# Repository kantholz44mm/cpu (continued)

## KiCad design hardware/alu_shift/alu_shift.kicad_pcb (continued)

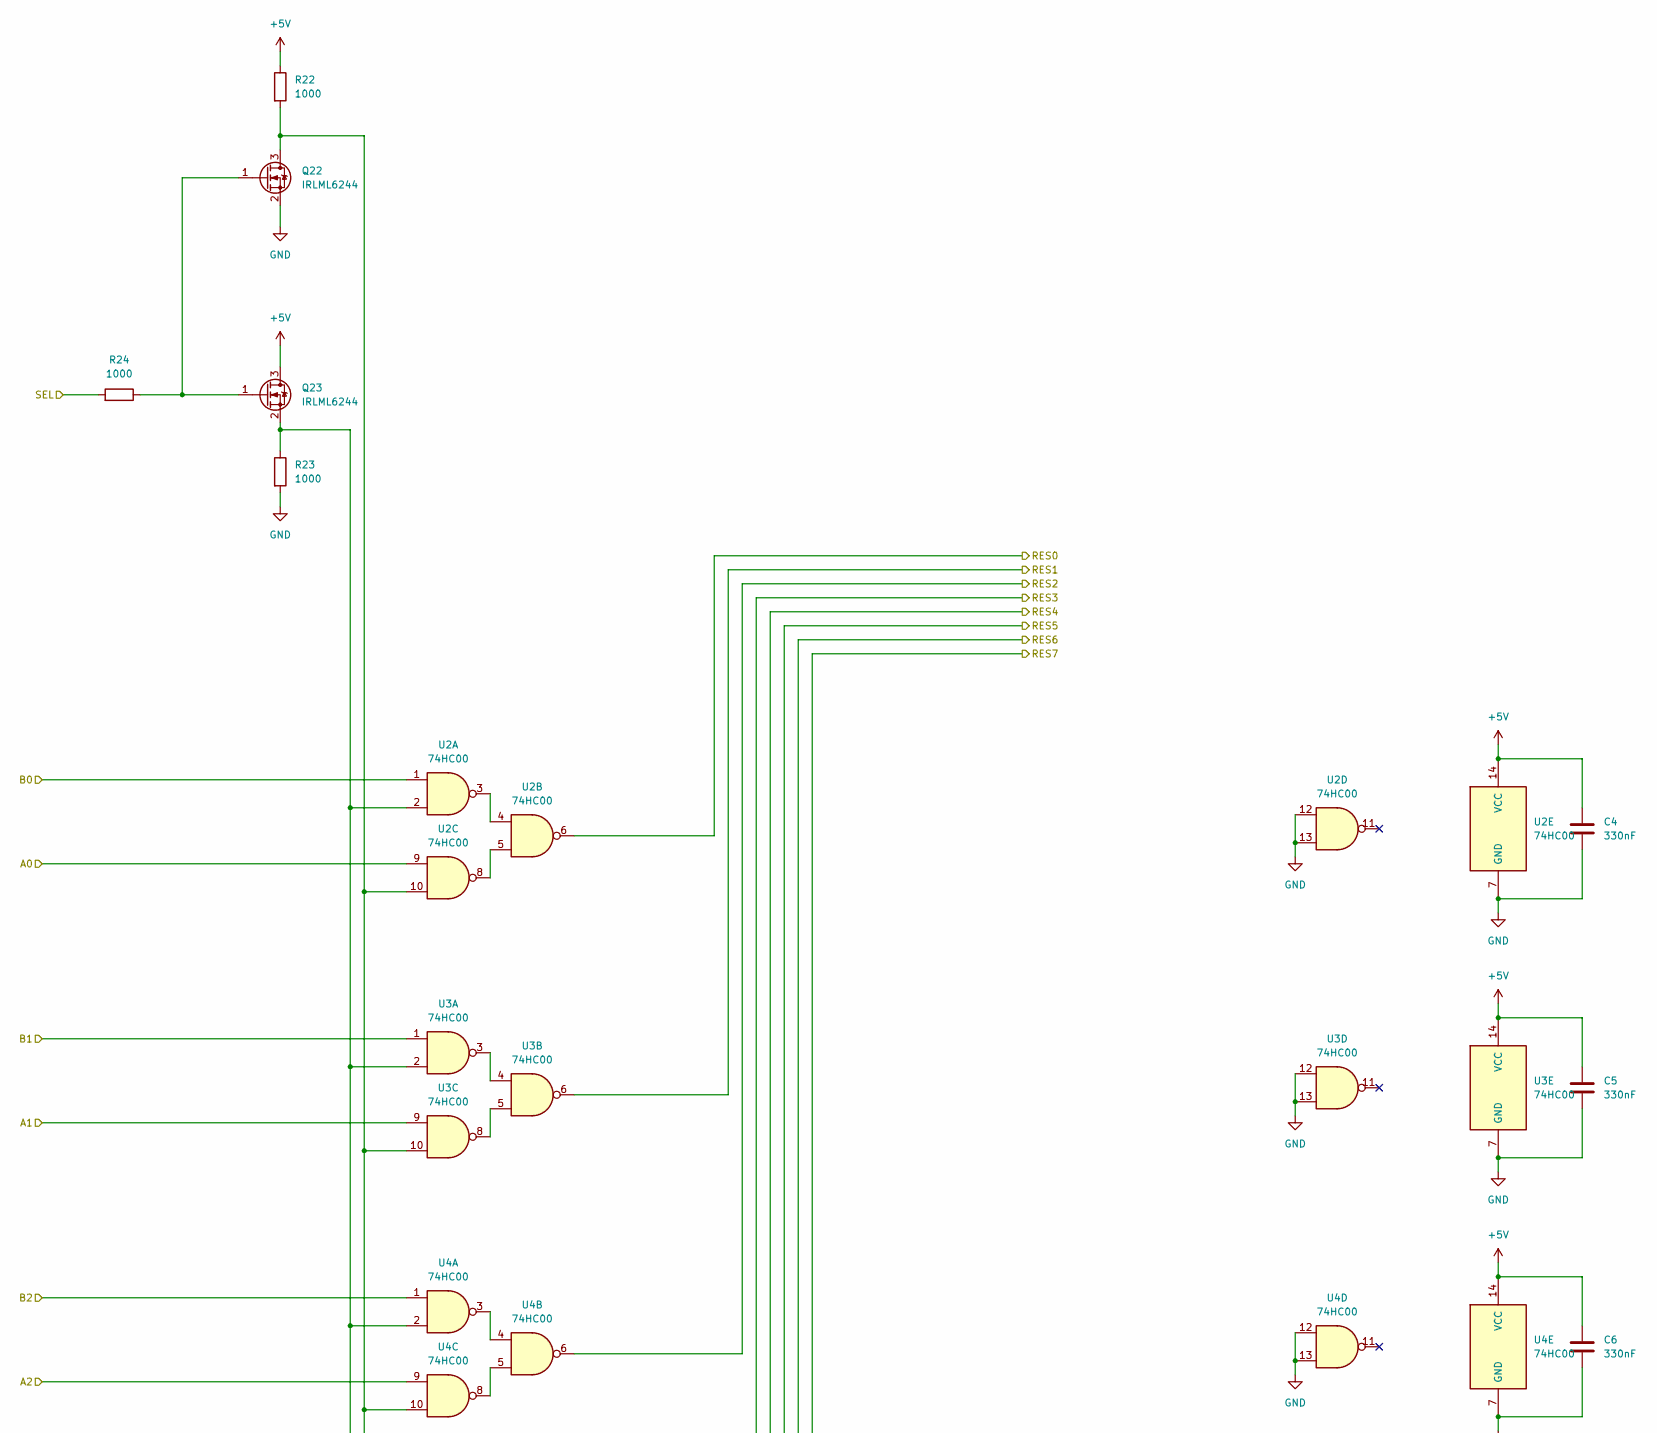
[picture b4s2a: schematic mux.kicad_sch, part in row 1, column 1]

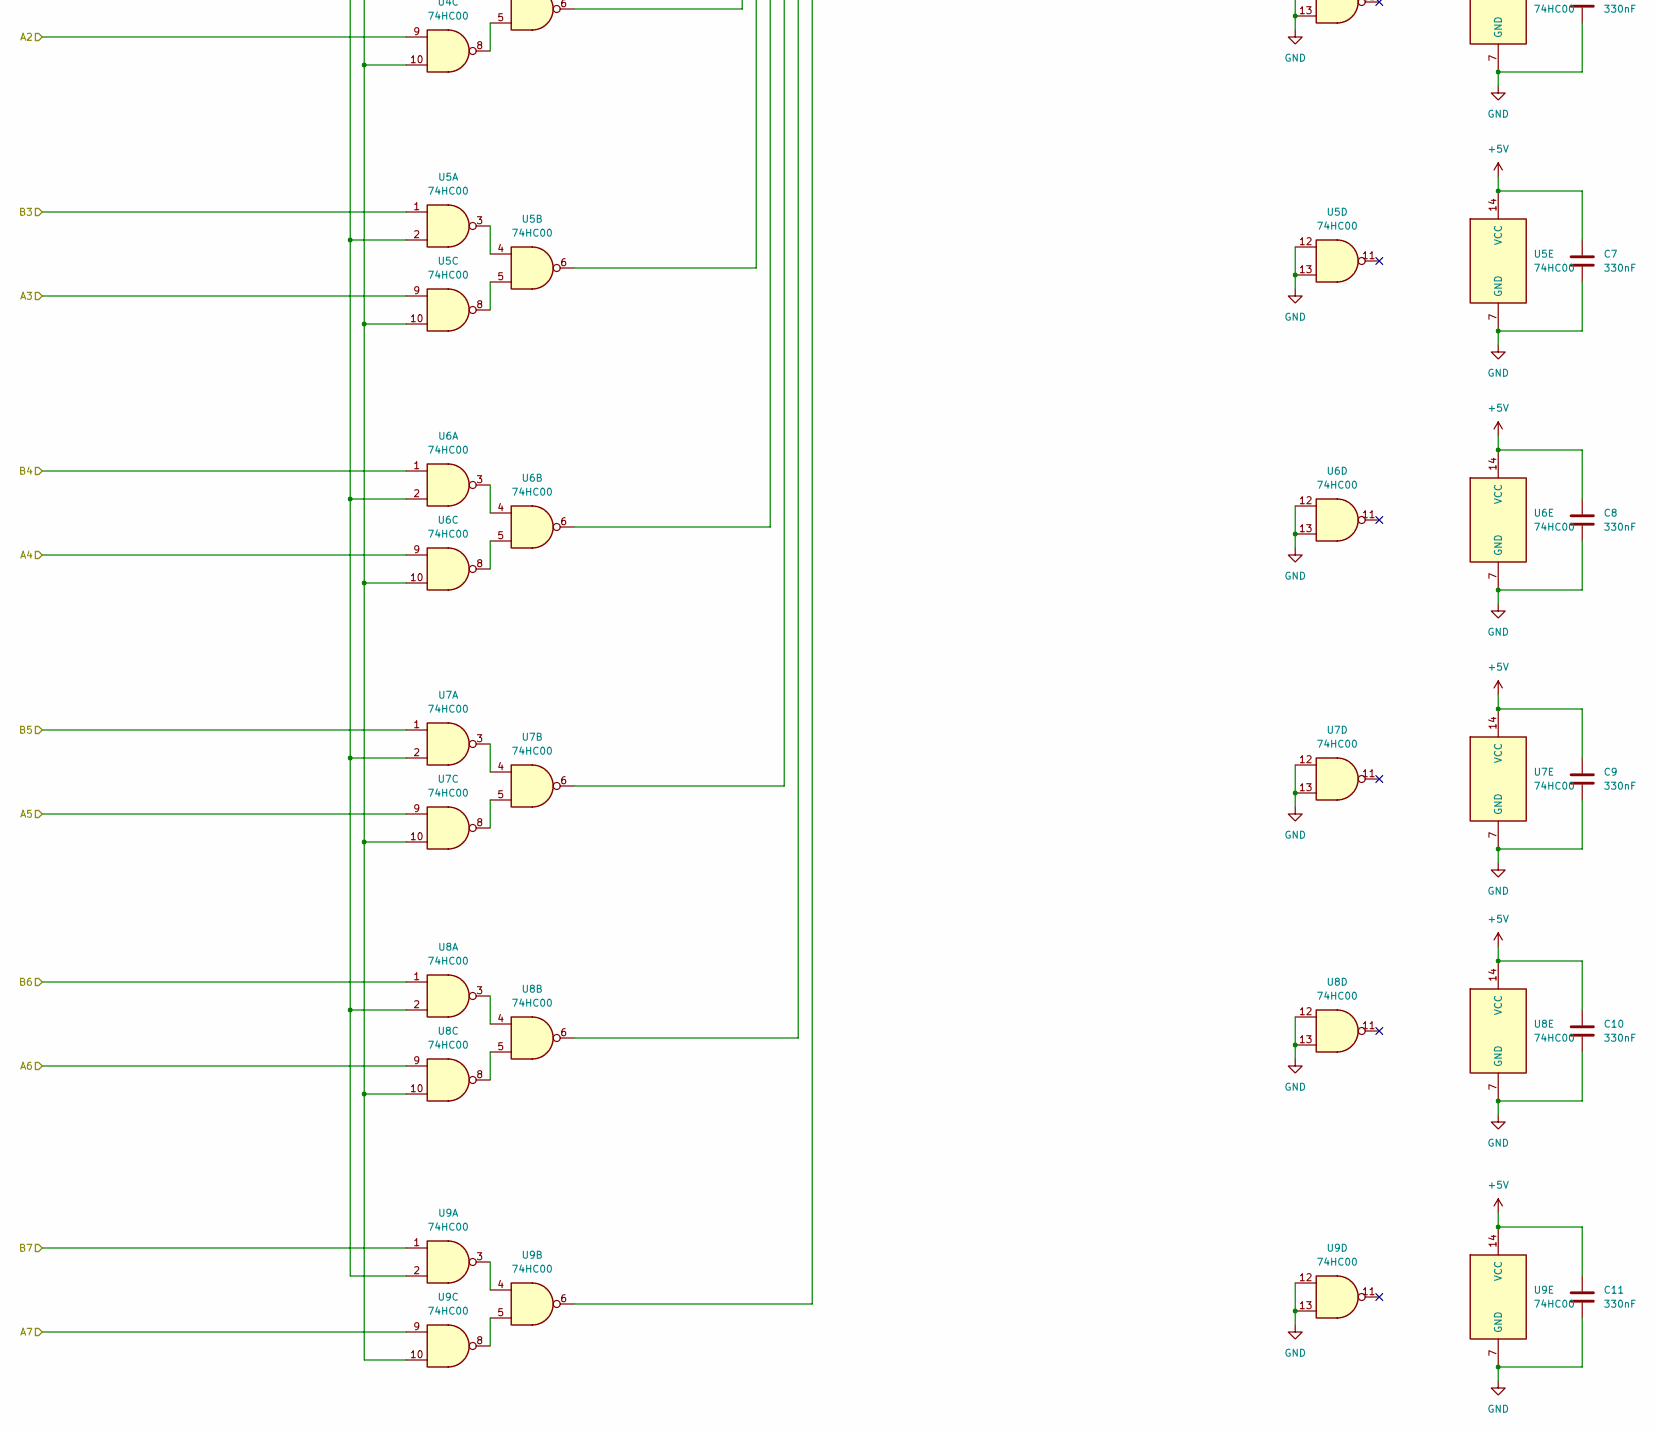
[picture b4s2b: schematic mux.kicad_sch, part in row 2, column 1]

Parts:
C4, C5, C6, C7, C8, C9, C10, C11: 330nF; C_0603_1608Metric_Pad1.08x0.95mm_HandSolder; LCSC C2918485
Q22, Q23: IRLML6244; SOT-23-3; LCSC C5123965
R22, R23, R24: 1000; R_0603_1608Metric_Pad0.98x0.95mm_HandSolder; LCSC C21190
U2, U3, U4, U5, U6, U7, U8, U9: 74HC00; SOIC-14_3.9x8.7mm_P1.27mm; LCSC C5586

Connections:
+5V: C4.1, C5.1, C6.1, C7.1, C8.1, C9.1, C10.1, C11.1, Q23.3 (D), R22.1, U2.14 (VCC), U3.14 (VCC), U4.14 (VCC), U5.14 (VCC), U6.14 (VCC), U7.14 (VCC), U8.14 (VCC), U9.14 (VCC); also elsewhere on the board
/MuxLeft1/A0: U2.9, U3.1; also elsewhere on the board
/MuxLeft1/A1: U3.9, U4.1; also elsewhere on the board
/MuxLeft1/A2: U4.9, U5.1; also elsewhere on the board
/MuxLeft1/A3: U5.9, U6.1; also elsewhere on the board
/MuxLeft1/A4: U6.9, U7.1; also elsewhere on the board
/MuxLeft1/A5: U7.9, U8.1; also elsewhere on the board
/MuxLeft1/A6: U8.9, U9.1; also elsewhere on the board
/MuxLeft1/A7: U9.9; also elsewhere on the board
/MuxLeft1/B0: U2.1; also elsewhere on the board
/MuxLeft1/RES0: U2.6; also elsewhere on the board
/MuxLeft1/RES1: U3.6; also elsewhere on the board
/MuxLeft1/RES2: U4.6; also elsewhere on the board
/MuxLeft1/RES3: U5.6; also elsewhere on the board
/MuxLeft1/RES4: U6.6; also elsewhere on the board
/MuxLeft1/RES5: U7.6; also elsewhere on the board
/MuxLeft1/RES6: U8.6; also elsewhere on the board
/MuxLeft1/RES7: U9.6; also elsewhere on the board
/MuxLeft1/SEL: R24.2; also elsewhere on the board
GND: C4.2, C5.2, C6.2, C7.2, C8.2, C9.2, C10.2, C11.2, Q22.2 (S), R23.2, U2.7 (GND), U2.12, U2.13, U3.7 (GND), U3.12, U3.13, U4.7 (GND), U4.12, U4.13, U5.7 (GND), U5.12, U5.13, U6.7 (GND), U6.12, U6.13, U7.7 (GND), U7.12, U7.13, U8.7 (GND), U8.12, U8.13, U9.7 (GND), U9.12, U9.13; also elsewhere on the board
unnamed: Q22.3 (D), R22.2, U2.10, U3.10, U4.10, U5.10, U6.10, U7.10, U8.10, U9.10
unnamed: Q22.1 (G), Q23.1 (G), R24.1
unnamed: Q23.2 (S), R23.1, U2.2, U3.2, U4.2, U5.2, U6.2, U7.2, U8.2, U9.2
unnamed: U2.3, U2.4
unnamed: U2.5, U2.8
unnamed: U3.3, U3.4
unnamed: U3.5, U3.8
unnamed: U4.3, U4.4
unnamed: U4.5, U4.8
unnamed: U5.3, U5.4
unnamed: U5.5, U5.8
unnamed: U6.3, U6.4
unnamed: U6.5, U6.8
unnamed: U7.3, U7.4
unnamed: U7.5, U7.8
unnamed: U8.3, U8.4
unnamed: U8.5, U8.8
unnamed: U9.3, U9.4
unnamed: U9.5, U9.8

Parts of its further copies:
C14, C15, C16, C17, C18, C19, C20, C21, C24, C25, C26, C27, C28, C29, C30, C31, C34, C35, C36, C37, C38, C39, C40, C41, C44, C45, C46, C47, C48, C49, C50, C51, C54, C55, C56, C57, C58, C59, C60, C61, C64, C65, C66, C67, C68, C69, C70, C71: 330nF; C_0603_1608Metric_Pad1.08x0.95mm_HandSolder; LCSC C2918485
Q24, Q25, Q26, Q27, Q28, Q29, Q30, Q31, Q32, Q33, Q34, Q35: IRLML6244; SOT-23-3; LCSC C5123965
R25, R26, R27, R28, R29, R30, R31, R32, R33, R34, R35, R36, R37, R38, R39, R40, R41, R42: 1000; R_0603_1608Metric_Pad0.98x0.95mm_HandSolder; LCSC C21190
U10, U11, U12, U13, U14, U15, U16, U17, U18, U19, U20, U21, U22, U23, U24, U25, U26, U27, U28, U29, U30, U31, U32, U33, U34, U35, U36, U37, U38, U39, U40, U41, U42, U43, U44, U45, U46, U47, U48, U49, U50, U51, U52, U53, U54, U55, U56, U57: 74HC00; SOIC-14_3.9x8.7mm_P1.27mm; LCSC C5586

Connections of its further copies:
+5V: C14.1, C15.1, C16.1, C17.1, C18.1, C19.1, C20.1, C21.1, C24.1, C25.1, C26.1, C27.1, C28.1, C29.1, C30.1, C31.1, C34.1, C35.1, C36.1, C37.1, C38.1, C39.1, C40.1, C41.1, C44.1, C45.1, C46.1, C47.1, C48.1, C49.1, C50.1, C51.1, C54.1, C55.1, C56.1, C57.1, C58.1, C59.1, C60.1, C61.1, C64.1, C65.1, C66.1, C67.1, C68.1, C69.1, C70.1, C71.1, Q25.3 (D), Q27.3 (D), Q29.3 (D), Q31.3 (D), Q33.3 (D), Q35.3 (D), R25.1, R28.1, R31.1, R34.1, R37.1, R40.1, U10.14 (VCC), U11.14 (VCC), U12.14 (VCC), U13.14 (VCC), U14.14 (VCC), U15.14 (VCC), U16.14 (VCC), U17.14 (VCC), U18.14 (VCC), U19.14 (VCC), U20.14 (VCC), U21.14 (VCC), U22.14 (VCC), U23.14 (VCC), U24.14 (VCC), U25.14 (VCC), U26.14 (VCC), U27.14 (VCC), U28.14 (VCC), U29.14 (VCC), U30.14 (VCC), U31.14 (VCC), U32.14 (VCC), U33.14 (VCC), U34.14 (VCC), U35.14 (VCC), U36.14 (VCC), U37.14 (VCC), U38.14 (VCC), U39.14 (VCC), U40.14 (VCC), U41.14 (VCC), U42.14 (VCC), U43.14 (VCC), U44.14 (VCC), U45.14 (VCC), U46.14 (VCC), U47.14 (VCC), U48.14 (VCC), U49.14 (VCC), U50.14 (VCC), U51.14 (VCC), U52.14 (VCC), U53.14 (VCC), U54.14 (VCC), U55.14 (VCC), U56.14 (VCC), U57.14 (VCC); also elsewhere on the board
/MuxLeft1/A0: U10.9; also elsewhere on the board
/MuxLeft1/A1: U10.1, U11.9; also elsewhere on the board
/MuxLeft1/A2: U11.1, U12.9; also elsewhere on the board
/MuxLeft1/A3: U12.1, U13.9; also elsewhere on the board
/MuxLeft1/A4: U13.1, U14.9; also elsewhere on the board
/MuxLeft1/A5: U14.1, U15.9; also elsewhere on the board
/MuxLeft1/A6: U15.1, U16.9; also elsewhere on the board
/MuxLeft1/A7: U16.1, U17.9; also elsewhere on the board
/MuxLeft1/B0: U17.1, U24.1, U25.1, U30.1, U31.1, U32.1, U33.1, U42.1, U43.1, U44.1, U45.1, U50.1, U51.1; also elsewhere on the board
/MuxLeft1/RES0: U50.9, U52.1; also elsewhere on the board
/MuxLeft1/RES1: U51.9, U53.1; also elsewhere on the board
/MuxLeft1/RES2: U52.9, U54.1; also elsewhere on the board
/MuxLeft1/RES3: U53.9, U55.1; also elsewhere on the board
/MuxLeft1/RES4: U54.9, U56.1; also elsewhere on the board
/MuxLeft1/RES5: U55.9, U57.1; also elsewhere on the board
/MuxLeft1/RES6: U56.9; also elsewhere on the board
/MuxLeft1/RES7: U57.9; also elsewhere on the board
/MuxLeft1/SEL: R27.2; also elsewhere on the board
/MuxLeft2/RES0: U42.9, U46.1, U50.6; also elsewhere on the board
/MuxLeft2/RES1: U43.9, U47.1, U51.6; also elsewhere on the board
/MuxLeft2/RES2: U44.9, U48.1, U52.6; also elsewhere on the board
/MuxLeft2/RES3: U45.9, U49.1, U53.6; also elsewhere on the board
/MuxLeft2/RES4: U46.9, U54.6; also elsewhere on the board
/MuxLeft2/RES5: U47.9, U55.6; also elsewhere on the board
/MuxLeft2/RES6: U48.9, U56.6; also elsewhere on the board
/MuxLeft2/RES7: U49.9, U57.6; also elsewhere on the board
/MuxLeft2/SEL: R30.2, R42.2; also elsewhere on the board
/MuxLeft4/RES0: U34.9, U42.6; also elsewhere on the board
/MuxLeft4/RES1: U35.9, U43.6; also elsewhere on the board
/MuxLeft4/RES2: U36.9, U44.6; also elsewhere on the board
/MuxLeft4/RES3: U37.9, U45.6; also elsewhere on the board
/MuxLeft4/RES4: U38.9, U46.6; also elsewhere on the board
/MuxLeft4/RES5: U39.9, U47.6; also elsewhere on the board
/MuxLeft4/RES6: U40.9, U48.6; also elsewhere on the board
/MuxLeft4/RES7: U41.9, U49.6; also elsewhere on the board
/MuxLeft4/SEL: R33.2, R39.2; also elsewhere on the board
/MuxResult/B0: U26.6, U34.1; also elsewhere on the board
/MuxResult/B1: U27.6, U35.1; also elsewhere on the board
/MuxResult/B2: U28.6, U36.1; also elsewhere on the board
/MuxResult/B3: U29.6, U37.1; also elsewhere on the board
/MuxResult/B4: U30.6, U38.1; also elsewhere on the board
/MuxResult/B5: U31.6, U39.1; also elsewhere on the board
/MuxResult/B6: U32.6, U40.1; also elsewhere on the board
/MuxResult/B7: U33.6, U41.1; also elsewhere on the board
/MuxResult/RES0: U34.6; also elsewhere on the board
/MuxResult/RES1: U35.6; also elsewhere on the board
/MuxResult/RES2: U36.6; also elsewhere on the board
/MuxResult/RES3: U37.6; also elsewhere on the board
/MuxResult/RES4: U38.6; also elsewhere on the board
/MuxResult/RES5: U39.6; also elsewhere on the board
/MuxResult/RES6: U40.6; also elsewhere on the board
/MuxResult/RES7: U41.6; also elsewhere on the board
/MuxResult/SEL: R36.2; also elsewhere on the board
/MuxRight1/RES0: U10.6, U18.9; also elsewhere on the board
/MuxRight1/RES1: U11.6, U19.9; also elsewhere on the board
/MuxRight1/RES2: U12.6, U18.1, U20.9; also elsewhere on the board
/MuxRight1/RES3: U13.6, U19.1, U21.9; also elsewhere on the board
/MuxRight1/RES4: U14.6, U20.1, U22.9; also elsewhere on the board
/MuxRight1/RES5: U15.6, U21.1, U23.9; also elsewhere on the board
/MuxRight1/RES6: U16.6, U22.1, U24.9; also elsewhere on the board
/MuxRight1/RES7: U17.6, U23.1, U25.9; also elsewhere on the board
/MuxRight2/RES0: U18.6, U26.9; also elsewhere on the board
/MuxRight2/RES1: U19.6, U27.9; also elsewhere on the board
/MuxRight2/RES2: U20.6, U28.9; also elsewhere on the board
/MuxRight2/RES3: U21.6, U29.9; also elsewhere on the board
/MuxRight2/RES4: U22.6, U26.1, U30.9; also elsewhere on the board
/MuxRight2/RES5: U23.6, U27.1, U31.9; also elsewhere on the board
/MuxRight2/RES6: U24.6, U28.1, U32.9; also elsewhere on the board
/MuxRight2/RES7: U25.6, U29.1, U33.9; also elsewhere on the board
GND: C14.2, C15.2, C16.2, C17.2, C18.2, C19.2, C20.2, C21.2, C24.2, C25.2, C26.2, C27.2, C28.2, C29.2, C30.2, C31.2, C34.2, C35.2, C36.2, C37.2, C38.2, C39.2, C40.2, C41.2, C44.2, C45.2, C46.2, C47.2, C48.2, C49.2, C50.2, C51.2, C54.2, C55.2, C56.2, C57.2, C58.2, C59.2, C60.2, C61.2, C64.2, C65.2, C66.2, C67.2, C68.2, C69.2, C70.2, C71.2, Q24.2 (S), Q26.2 (S), Q28.2 (S), Q30.2 (S), Q32.2 (S), Q34.2 (S), R26.2, R29.2, R32.2, R35.2, R38.2, R41.2, U10.7 (GND), U10.12, U10.13, U11.7 (GND), U11.12, U11.13, U12.7 (GND), U12.12, U12.13, U13.7 (GND), U13.12, U13.13, U14.7 (GND), U14.12, U14.13, U15.7 (GND), U15.12, U15.13, U16.7 (GND), U16.12, U16.13, U17.7 (GND), U17.12, U17.13, U18.7 (GND), U18.12, U18.13, U19.7 (GND), U19.12, U19.13, U20.7 (GND), U20.12, U20.13, U21.7 (GND), U21.12, U21.13, U22.7 (GND), U22.12, U22.13, U23.7 (GND), U23.12, U23.13, U24.7 (GND), U24.12, U24.13, U25.7 (GND), U25.12, U25.13, U26.7 (GND), U26.12, U26.13, U27.7 (GND), U27.12, U27.13, U28.7 (GND), U28.12, U28.13, U29.7 (GND), U29.12, U29.13, U30.7 (GND), U30.12, U30.13, U31.7 (GND), U31.12, U31.13, U32.7 (GND), U32.12, U32.13, U33.7 (GND), U33.12, U33.13, U34.7 (GND), U34.12, U34.13, U35.7 (GND), U35.12, U35.13, U36.7 (GND), U36.12, U36.13, U37.7 (GND), U37.12, U37.13, U38.7 (GND), U38.12, U38.13, U39.7 (GND), U39.12, U39.13, U40.7 (GND), U40.12, U40.13, U41.7 (GND), U41.12, U41.13, U42.7 (GND), U42.12, U42.13, U43.7 (GND), U43.12, U43.13, U44.7 (GND), U44.12, U44.13, U45.7 (GND), U45.12, U45.13, U46.7 (GND), U46.12, U46.13, U47.7 (GND), U47.12, U47.13, U48.7 (GND), U48.12, U48.13, U49.7 (GND), U49.12, U49.13, U50.7 (GND), U50.12, U50.13, U51.7 (GND), U51.12, U51.13, U52.7 (GND), U52.12, U52.13, U53.7 (GND), U53.12, U53.13, U54.7 (GND), U54.12, U54.13, U55.7 (GND), U55.12, U55.13, U56.7 (GND), U56.12, U56.13, U57.7 (GND), U57.12, U57.13; also elsewhere on the board
unnamed: Q24.3 (D), R25.2, U10.10, U11.10, U12.10, U13.10, U14.10, U15.10, U16.10, U17.10
unnamed: Q24.1 (G), Q25.1 (G), R27.1
unnamed: Q25.2 (S), R26.1, U10.2, U11.2, U12.2, U13.2, U14.2, U15.2, U16.2, U17.2
unnamed: Q26.3 (D), R28.2, U18.10, U19.10, U20.10, U21.10, U22.10, U23.10, U24.10, U25.10
unnamed: Q26.1 (G), Q27.1 (G), R30.1
unnamed: Q27.2 (S), R29.1, U18.2, U19.2, U20.2, U21.2, U22.2, U23.2, U24.2, U25.2
unnamed: Q28.3 (D), R31.2, U26.10, U27.10, U28.10, U29.10, U30.10, U31.10, U32.10, U33.10
unnamed: Q28.1 (G), Q29.1 (G), R33.1
unnamed: Q29.2 (S), R32.1, U26.2, U27.2, U28.2, U29.2, U30.2, U31.2, U32.2, U33.2
unnamed: Q30.3 (D), R34.2, U34.10, U35.10, U36.10, U37.10, U38.10, U39.10, U40.10, U41.10
unnamed: Q30.1 (G), Q31.1 (G), R36.1
unnamed: Q31.2 (S), R35.1, U34.2, U35.2, U36.2, U37.2, U38.2, U39.2, U40.2, U41.2
unnamed: Q32.3 (D), R37.2, U42.10, U43.10, U44.10, U45.10, U46.10, U47.10, U48.10, U49.10
unnamed: Q32.1 (G), Q33.1 (G), R39.1
unnamed: Q33.2 (S), R38.1, U42.2, U43.2, U44.2, U45.2, U46.2, U47.2, U48.2, U49.2
unnamed: Q34.3 (D), R40.2, U50.10, U51.10, U52.10, U53.10, U54.10, U55.10, U56.10, U57.10
unnamed: Q34.1 (G), Q35.1 (G), R42.1
unnamed: Q35.2 (S), R41.1, U50.2, U51.2, U52.2, U53.2, U54.2, U55.2, U56.2, U57.2
unnamed: U10.3, U10.4
unnamed: U10.5, U10.8
unnamed: U11.3, U11.4
unnamed: U11.5, U11.8
unnamed: U12.3, U12.4
unnamed: U12.5, U12.8
unnamed: U13.3, U13.4
unnamed: U13.5, U13.8
unnamed: U14.3, U14.4
unnamed: U14.5, U14.8
unnamed: U15.3, U15.4
unnamed: U15.5, U15.8
unnamed: U16.3, U16.4
unnamed: U16.5, U16.8
unnamed: U17.3, U17.4
unnamed: U17.5, U17.8
unnamed: U18.3, U18.4
unnamed: U18.5, U18.8
unnamed: U19.3, U19.4
unnamed: U19.5, U19.8
unnamed: U20.3, U20.4
unnamed: U20.5, U20.8
unnamed: U21.3, U21.4
unnamed: U21.5, U21.8
unnamed: U22.3, U22.4
unnamed: U22.5, U22.8
unnamed: U23.3, U23.4
unnamed: U23.5, U23.8
unnamed: U24.3, U24.4
unnamed: U24.5, U24.8
unnamed: U25.3, U25.4
unnamed: U25.5, U25.8
unnamed: U26.3, U26.4
unnamed: U26.5, U26.8
unnamed: U27.3, U27.4
unnamed: U27.5, U27.8
unnamed: U28.3, U28.4
unnamed: U28.5, U28.8
unnamed: U29.3, U29.4
unnamed: U29.5, U29.8
unnamed: U30.3, U30.4
unnamed: U30.5, U30.8
unnamed: U31.3, U31.4
unnamed: U31.5, U31.8
unnamed: U32.3, U32.4
unnamed: U32.5, U32.8
unnamed: U33.3, U33.4
unnamed: U33.5, U33.8
unnamed: U34.3, U34.4
unnamed: U34.5, U34.8
unnamed: U35.3, U35.4
unnamed: U35.5, U35.8
unnamed: U36.3, U36.4
unnamed: U36.5, U36.8
unnamed: U37.3, U37.4
unnamed: U37.5, U37.8
unnamed: U38.3, U38.4
unnamed: U38.5, U38.8
unnamed: U39.3, U39.4
unnamed: U39.5, U39.8
unnamed: U40.3, U40.4
unnamed: U40.5, U40.8
unnamed: U41.3, U41.4
unnamed: U41.5, U41.8
unnamed: U42.3, U42.4
unnamed: U42.5, U42.8
unnamed: U43.3, U43.4
unnamed: U43.5, U43.8
unnamed: U44.3, U44.4
unnamed: U44.5, U44.8
unnamed: U45.3, U45.4
unnamed: U45.5, U45.8
unnamed: U46.3, U46.4
unnamed: U46.5, U46.8
unnamed: U47.3, U47.4
unnamed: U47.5, U47.8
unnamed: U48.3, U48.4
unnamed: U48.5, U48.8
unnamed: U49.3, U49.4
unnamed: U49.5, U49.8
unnamed: U50.3, U50.4
unnamed: U50.5, U50.8
unnamed: U51.3, U51.4
unnamed: U51.5, U51.8
unnamed: U52.3, U52.4
unnamed: U52.5, U52.8
unnamed: U53.3, U53.4
unnamed: U53.5, U53.8
unnamed: U54.3, U54.4
unnamed: U54.5, U54.8
unnamed: U55.3, U55.4
unnamed: U55.5, U55.8
unnamed: U56.3, U56.4
unnamed: U56.5, U56.8
unnamed: U57.3, U57.4
unnamed: U57.5, U57.8

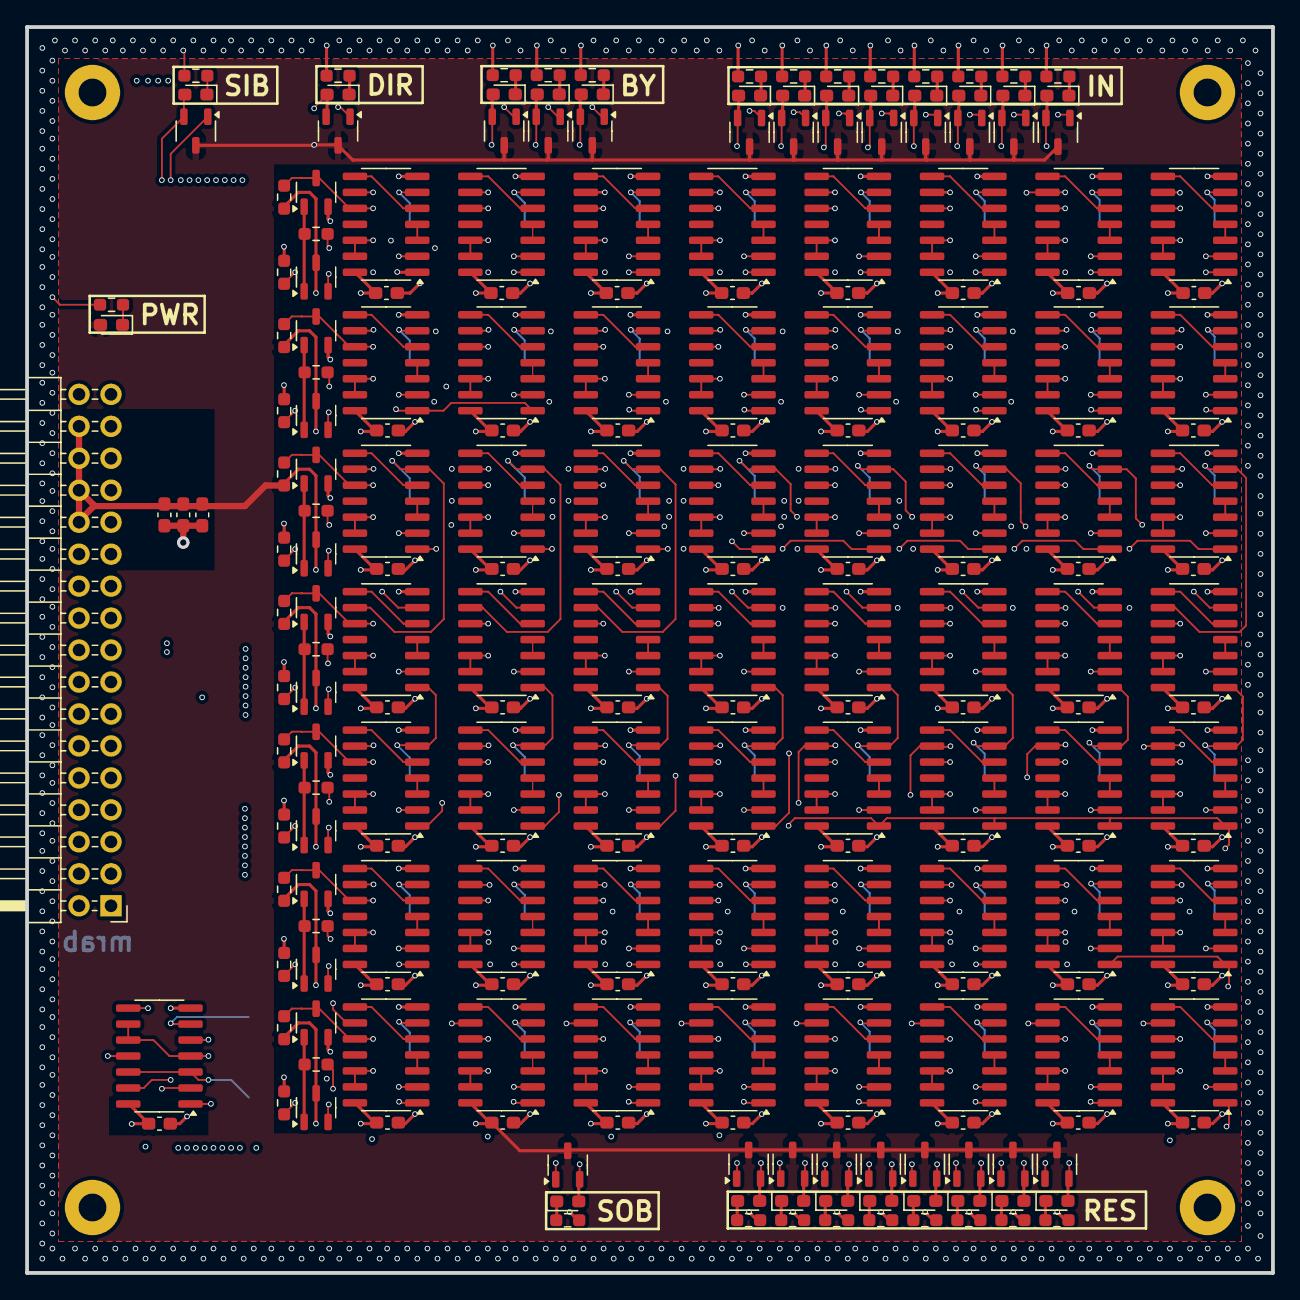
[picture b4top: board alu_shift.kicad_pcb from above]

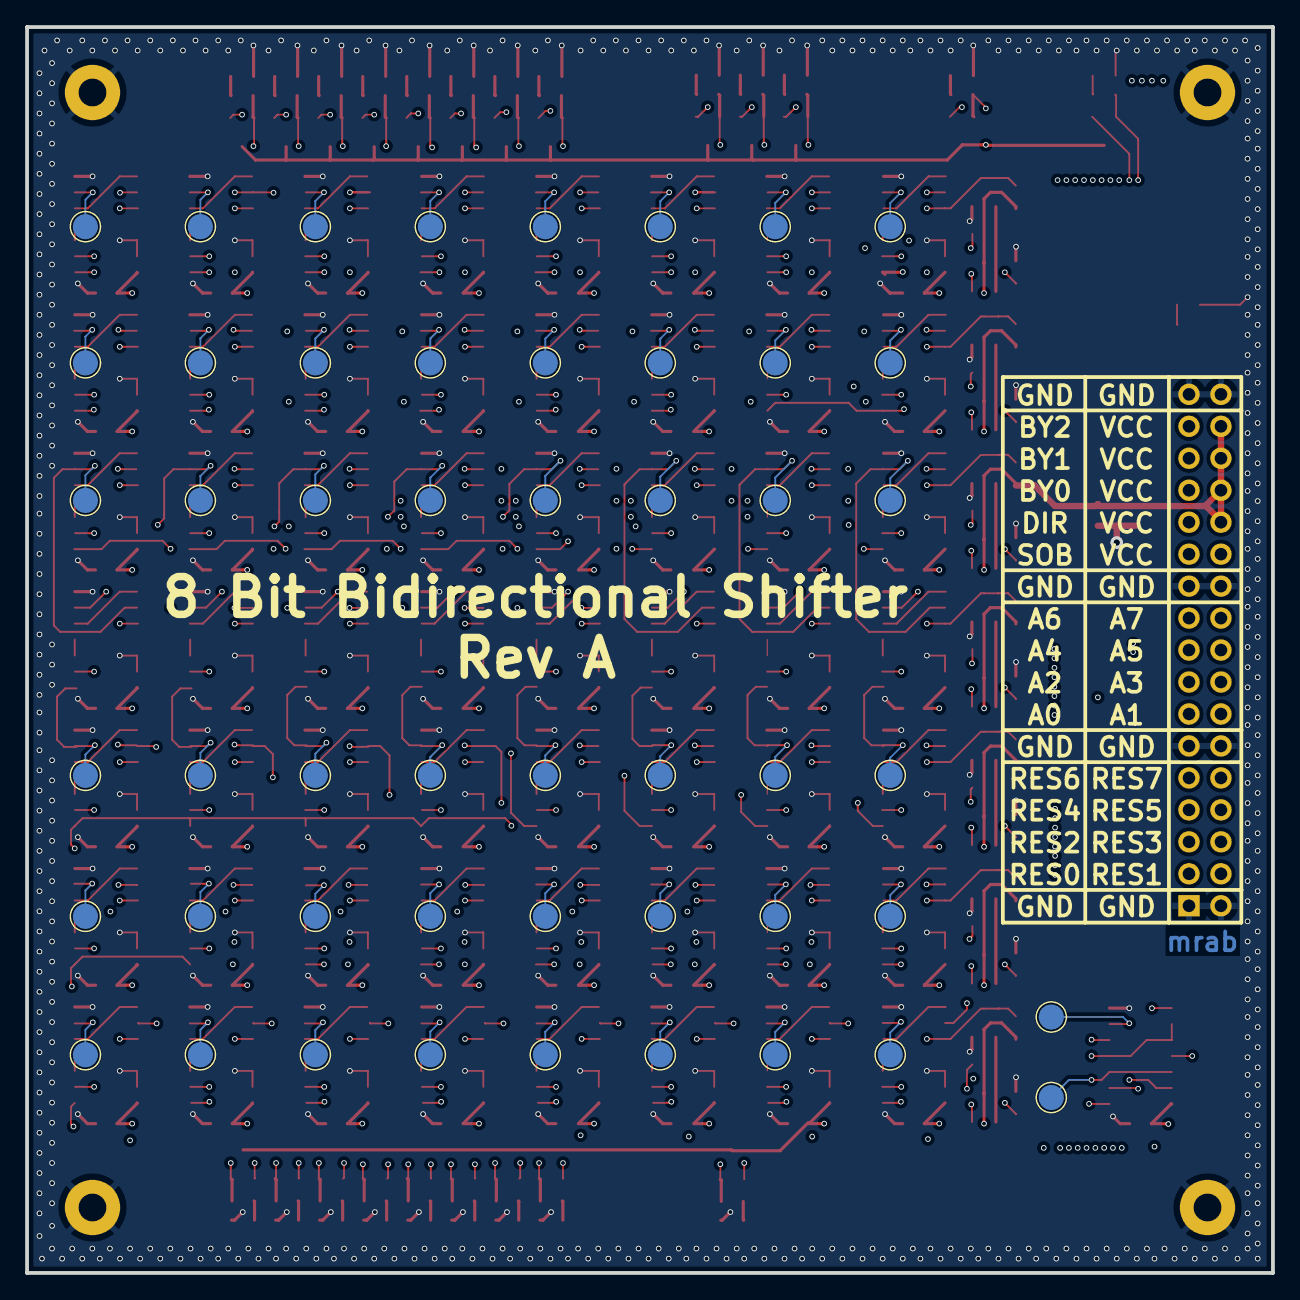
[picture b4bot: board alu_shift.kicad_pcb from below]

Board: 4 copper layers, 99.0 x 99.0 mm, 275 parts (50 on the bottom side), 253 nets.

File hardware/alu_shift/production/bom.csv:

Designator,Footprint,Quantity,Value,LCSC Part #
"C1, C10, C11, C14, C15, C16, C17, C18, C19, C20, C21, C24, C25, C26, C27, C28, C29, C30, C31, C34, C35, C36, C37, C38, C39, C4, C40, C41, C44, C45, C46, C47, C48, C49, C5, C50, C51, C54, C55, C56, C57, C58, C59, C6, C60, C61, C64, C65, C66, C67, C68, C69, C7, C70, C71, C8, C9",0603,57,330nF,C2918485
"C12, C2, C3",0603,3,10uF,C2909630
"D1, D10, D11, D12, D13, D14, D15, D16, D17, D18, D19, D2, D20, D21, D22, D23, D3, D4, D5, D6, D7, D8, D9",0603,23,LED,C84267
"Q1, Q10, Q11, Q12, Q13, Q14, Q15, Q16, Q17, Q18, Q19, Q2, Q20, Q21, Q22, Q23, Q24, Q25, Q26, Q27, Q28, Q29, Q3, Q30, Q31, Q32, Q33, Q34, Q35, Q36, Q4, Q5, Q6, Q7, Q8, Q9",SOT-23-3,36,IRLML6244,C5123965
"R1, R10, R11, R12, R13, R14, R15, R16, R17, R18, R19, R2, R20, R21, R22, R23, R24, R25, R26, R27, R28, R29, R3, R30, R31, R32, R33, R34, R35, R36, R37, R38, R39, R4, R40, R41, R42, R43, R44, R5, R6, R7, R8, R9",0603,44,1000,C21190
"U1, U10, U11, U12, U13, U14, U15, U16, U17, U18, U19, U2, U20, U21, U22, U23, U24, U25, U26, U27, U28, U29, U3, U30, U31, U32, U33, U34, U35, U36, U37, U38, U39, U4, U40, U41, U42, U43, U44, U45, U46, U47, U48, U49, U5, U50, U51, U52, U53, U54, U55, U56, U57, U6, U7, U8, U9",SOIC-14_3.9x8.7mm_P1.27mm,57,74HC00,C5586
